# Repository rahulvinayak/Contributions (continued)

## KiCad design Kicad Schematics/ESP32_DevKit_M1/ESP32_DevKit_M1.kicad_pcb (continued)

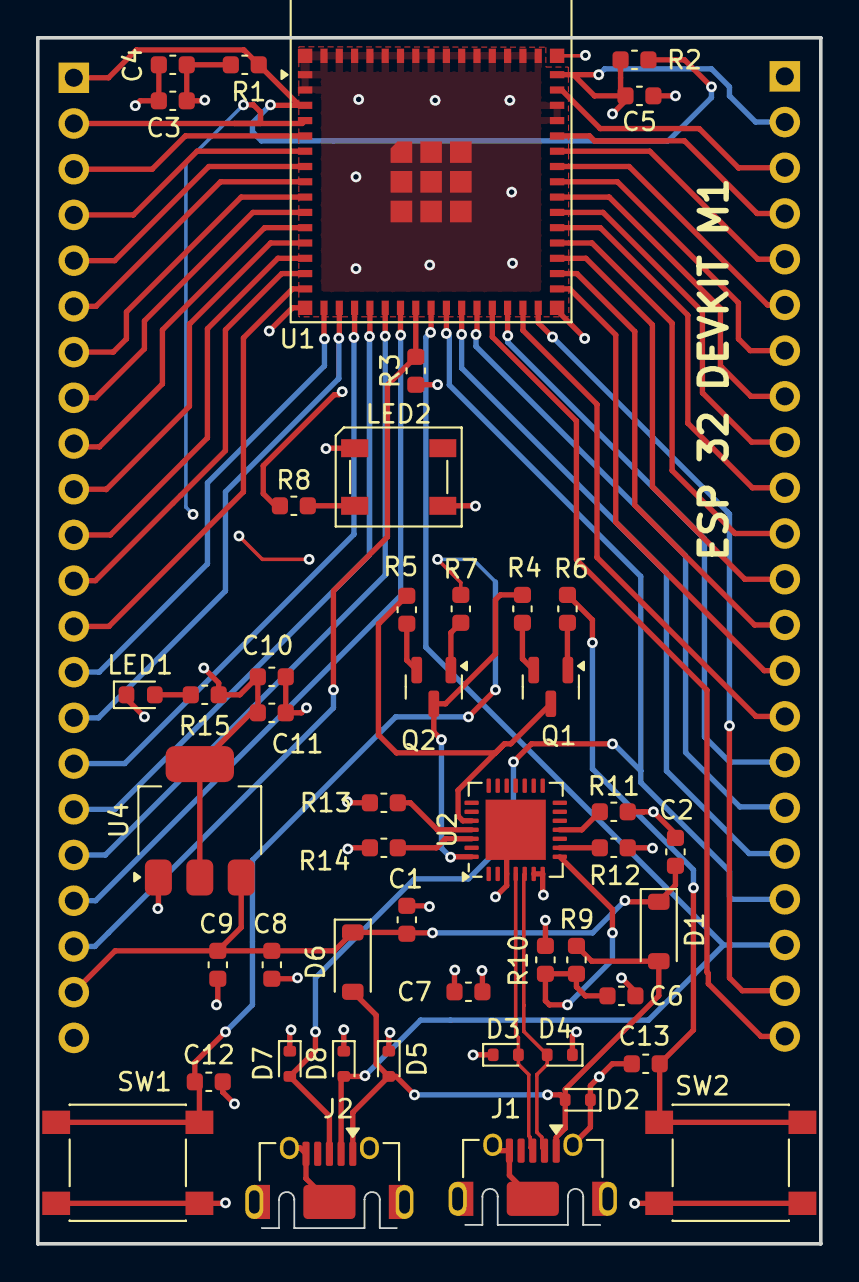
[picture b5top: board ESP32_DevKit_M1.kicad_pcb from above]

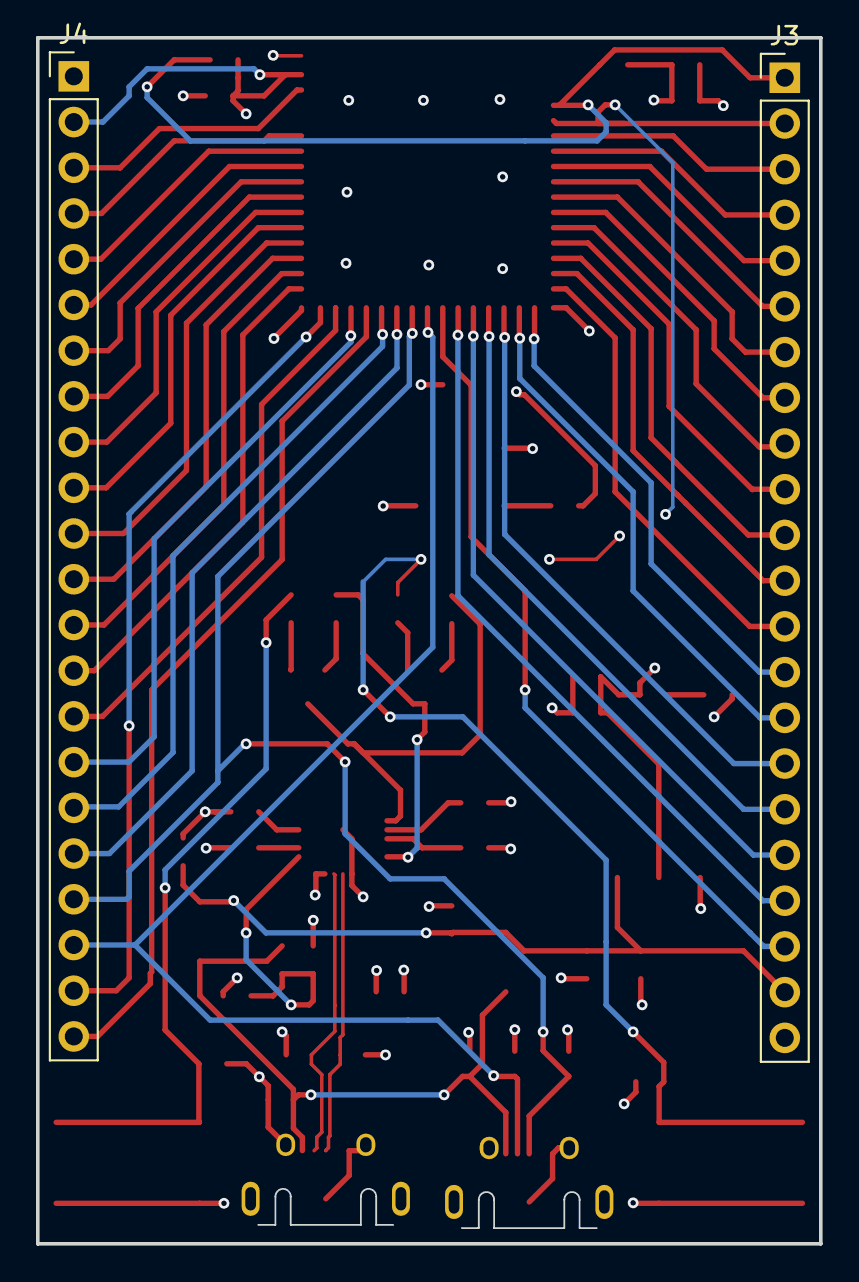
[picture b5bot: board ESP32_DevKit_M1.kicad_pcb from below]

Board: 4 copper layers, 43.5 x 67.0 mm, 49 parts (2 on the bottom side), 60 nets.

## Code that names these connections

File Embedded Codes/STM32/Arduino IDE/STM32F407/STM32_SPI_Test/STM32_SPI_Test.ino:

/*
 * STM32 SPI Slave - Receive Data from ESP32
 * 
 * Hardware Setup:
 * ESP32 -> STM32
 * MOSI (GPIO23) -> MISO (PB4)
 * SCK (GPIO18)  -> SCK (PB3)
 * CS (GPIO5)    -> NSS (PB6) [optional]
 * GND           -> GND
 * 
 * This code receives data from ESP32 SPI master
 */

#include <SPI.h>

String receivedMessage = "";
bool messageComplete = false;

void setup() {
  Serial.begin(115200);
  while (!Serial);
  
  Serial.println("STM32 SPI Slave - Receiving from ESP32");
  Serial.println("Waiting for ESP32 data...");
  Serial.println();
  
  // Configure SPI pins for slave mode
  SPI.setMOSI(PB5);  // Not used but needed for init
  SPI.setMISO(PB4);  // This is our receive pin (connects to ESP32 MOSI)
  SPI.setSCLK(PB3);  // Clock from ESP32
  
  // Optional: Configure NSS/CS pin
  pinMode(PB6, INPUT);
  
  SPI.begin();
  SPI.beginTransaction(SPISettings(1000000, MSBFIRST, SPI_MODE0));
}

void loop() {
  // Check if CS is active (low) - optional if using CS
  bool csActive = (digitalRead(PB6) == LOW);
  
  // Receive data when CS is active or continuously if not using CS
  if (csActive || true) {  // Change to just 'csActive' if using CS properly
    
    // Receive byte from ESP32
    uint8_t receivedByte = SPI.transfer(0x00);  // Send dummy, receive actual data
    
    if (receivedByte != 0x00) {  // Valid data received
      
      // Add to message string
      receivedMessage += (char)receivedByte;
      
      // Display received byte
      Serial.print("Received byte: 0x");
      Serial.print(receivedByte, HEX);
      Serial.print(" ('");
      Serial.print((char)receivedByte);
      Serial.println("')");
      
      // Check if message is complete (you can modify this logic)
      if (receivedByte == '!' || receivedMessage.length() >= 20) {
        messageComplete = true;
      }
    }
  }
  
  // If CS goes high, consider message complete
  if (!csActive && receivedMessage.length() > 0) {
    messageComplete = true;
  }
  
  // Display complete message
  if (messageComplete && receivedMessage.length() > 0) {
    Serial.println();
    Serial.print("Complete message: \"");
    Serial.print(receivedMessage);
    Serial.println("\"");
    Serial.println();
    
    // Reset for next message
    receivedMessage = "";
    messageComplete = false;
  }
  
  delay(10);  // Small delay
}

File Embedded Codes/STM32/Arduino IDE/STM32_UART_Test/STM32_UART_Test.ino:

HardwareSerial MySerial1(PD6, PD5); // RX, TX
HardwareSerial MySerial2(PB7, PB6); // RX, TX

void setup() {
  MySerial1.begin(115200); // Set Serial Monitor Baud Rate to 115200
}

void loop() {
 MySerial1.println("UART Testing"); // Sends Message at Inverval of 1 sec
 delay(1000);
}

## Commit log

2025-08-31 Mass add and commit
